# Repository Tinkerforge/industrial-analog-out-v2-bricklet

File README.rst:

Industrial Analog Out Bricklet 2.0
==================================

This repository contains the firmware source code and the hardware design
files. The documentation generator configs can be found at
https://github.com/Tinkerforge/generators

Repository Content
------------------

software/:
 * examples/: Examples for all supported languages
 * build/: Compiled files
 * src/: Source code of firmware
 * Makefile: Makefile to build project

hardware/:
 * Contains KiCad project files and additionally schematics as PDF

datasheets/:
 * Contains datasheets for sensors and complex ICs that are used

Hardware
--------

The hardware is designed with the open source EDA Suite KiCad
(http://www.kicad.org). Before you are able to open the files,
you have to install the Tinkerforge kicad-libraries
(https://github.com/Tinkerforge/kicad-libraries). You can either clone
them directly in hardware/ or clone them in a separate folder and
symlink them into hardware/
(ln -s kicad_path/kicad-libraries project_path/hardware). After that you
can open the .pro file in hardware/ with KiCad and from there view and
modify the schematics and the PCB layout.

Software
--------

If you want to do your own Brick/Bricklet firmware development we highly
recommend that you use our build environment setup script and read the
tutorial (https://www.tinkerforge.com/en/doc/Tutorials/Tutorial_Build_Environment/Tutorial.html).

To compile the C code we recommend you to install the newest GNU Arm Embedded
Toolchain (https://launchpad.net/gcc-arm-embedded/+download).
You also need to install bricklib2 (https://github.com/Tinkerforge/bricklib2).

You can either clone it directly in software/src/ or clone it in a
separate folder and symlink it into software/src/
(ln -s bricklib_path/bricklib2 project_path/software/src/). Finally make sure to
have CMake installed (http://www.cmake.org/cmake/resources/software.html).

After that you can build the firmware by invoking make in software/.
The firmware (.zbin) can then be found in software/build/ and uploaded
with brickv (click button "Flashing" on start screen).

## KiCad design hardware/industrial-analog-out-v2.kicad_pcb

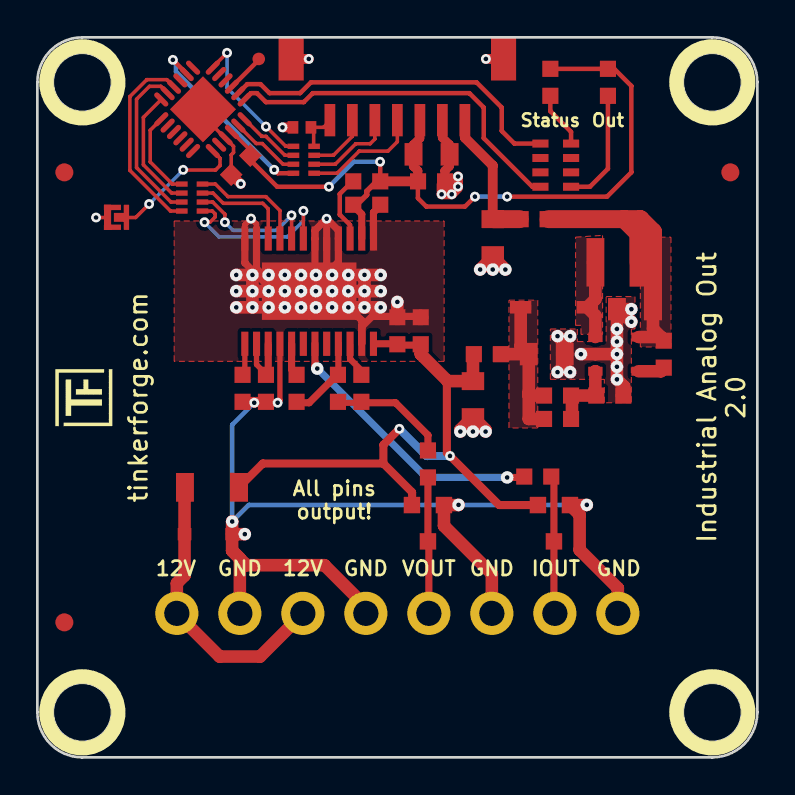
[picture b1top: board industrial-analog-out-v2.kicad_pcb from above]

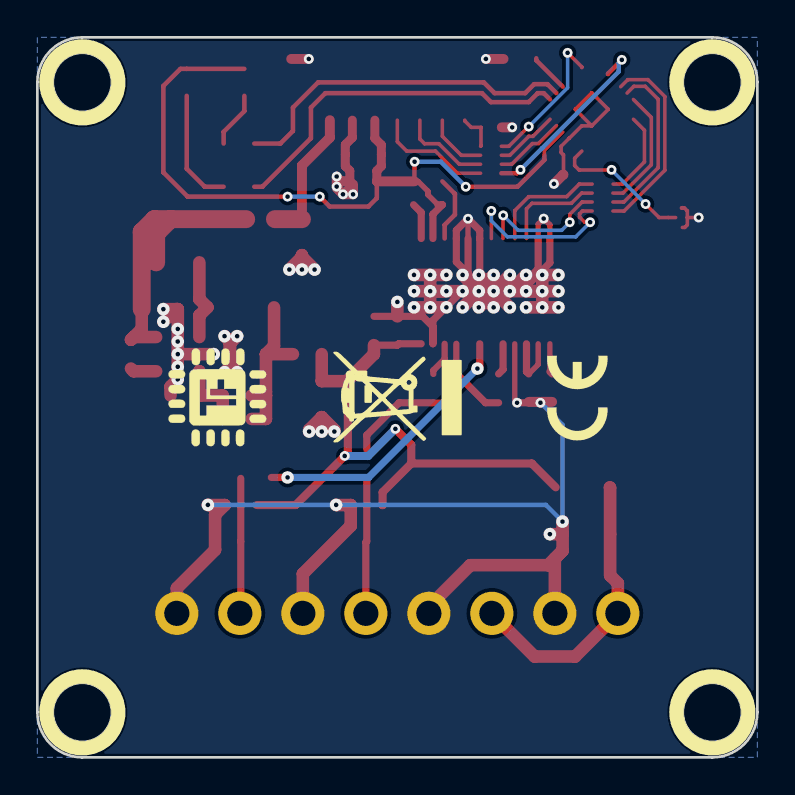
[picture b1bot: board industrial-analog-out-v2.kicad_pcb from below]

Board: 2 copper layers, 40.0 x 40.0 mm, 52 parts (2 on the bottom side), 42 nets.

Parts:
C1, C2, C5, C7: 4.7µF; C0805
C3: 10uF; C0805
C4: 270pF; C0603F
C6, C8, C9, C14: 100nF; C0603F
C10: 100pF; C0603F
C11: 1nF; C0603F
C12: 220pF; C0402F
C13: 1uF; C0603F
D1: B0520LW; SOD-123
D2, D3: DESD1P0RFW; SOT23-3
D4: CDSOD323-T15SC; SOD-323
D5, D6: blue; D0603F
F1: OZCJ0035FF2G; C1206
Fiducial_Mark: VAL**; Fiducial_Mark
Fiducial_Mark#2, Fiducial_Mark#3: VAL**; Fiducial_Mark
L1, L3, L4: FB; R0603F
L2: 10µH; NR3030
P1: CON-SENSOR2
P2: CONN_8; OQ_8P
P3: DEBUG; DEBUG_PAD
P4: BOOT; SolderJumper
R1: 1M; R0603F
R2: 13.3k; R0603F
R3: 118k; R0603F
R4: 10k; R0603F
R5: DNP; R0603F
R6, R7: 15; R0603F
R8: 10; R0603F
RP1, RP2: 82; 4X0402
RP3: 1k; 4X0603
U1: LMR62014X; SOT23-5
U2: XMC1100; QFN24-4x4mm-0.5mm
U3: DACX760; TSSOP24-44-PWR
U4, U5, U6, U7: DRILL; DRILL_NP
VAL: WEEE_7mm_back; WEEE_7mm
VAL#2: CE_5mm

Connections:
3V3: C3.1, C6.1, C13.1, C14.1, D5.1, D6.1, P1.3, R4.1, U2.10, U3.2
+5V: C1.2, L1.2, P1.1
+12V: C7.2, C9.2, C10.2, D2.2, D3.2, F1.1, L3.1, U3.24
GND: C1.1, C2.1, C3.2, C5.1, C6.2, C7.1, C8.2, C9.1, C10.1, C12.2, C13.2, C14.2, D2.1, D3.1, D4.2, P1.2, P1.EP, P2.2, P2.4, P2.6, P2.8, P4.1, R2.2, R5.2, U1.2, U2.9, U2.EXP, U3.1, U3.4, U3.5, U3.6, U3.11, U3.12, U3.16, U3.23
M-CLK: RP2.2, U3.8
M-CS: RP2.1, U3.7
M-MISO: RP2.3, U3.10
M-MOSI: RP2.4, U3.9
unnamed: C2.2, L1.1, L2.2, R1.1, U1.5
unnamed: C4.1, C5.2, D1.2, L3.2, R3.1
unnamed: C4.2, R2.1, R3.2, U1.3
unnamed: C8.1, U3.14, U3.15
unnamed: C11.1, R7.2, U3.21
unnamed: C11.2, U3.17
unnamed: C12.1, P1.7, RP1.4
unnamed: D1.1, L2.1, U1.1
unnamed: D2.3, L4.1, P2.5
unnamed: D3.3, P2.7, R8.1
unnamed: D4.1, F1.2, P2.1, P2.3
unnamed: D5.2, RP3.1
unnamed: D6.2, RP3.4
unnamed: L4.2, R6.1, R7.1
unnamed: P1.4, RP1.1
unnamed: P1.5, RP1.2
unnamed: P1.6, RP1.3
unnamed: P3.1, U2.15
unnamed: P4.2, U2.7
unnamed: R1.2, U1.4
unnamed: R4.2, U3.3
unnamed: R5.1, U3.13
unnamed: R6.2, U3.22
unnamed: R8.2, U3.19
unnamed: RP2.6, U2.24
unnamed: RP2.7, U2.23
unnamed: RP2.8, U2.22
unnamed: RP3.5, U2.13
unnamed: RP3.8, U2.14
P0.2: RP2.5, U2.1
S-CLK: RP1.7, U2.11
S-CS: RP1.8, U2.20
S-MISO: RP1.5, U2.18
S-MOSI: RP1.6, U2.12

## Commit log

2018-03-13 Add datasheet
2018-03-13 Add schematic
2018-03-13 Assign missing footprints
2018-03-13 Connect dac7760 to mcu
2018-03-13 Fix some pins
2018-03-13 Add layout
2018-03-13 Add all logos
2018-03-19 added second led, not fully routed
2018-03-19 routing finished, logo placement fixed
2018-03-19 fix status text
2018-04-10 Add auto-generated stub firmware
2018-04-10 Use correct pin defines for SPI, LEDs and debug
2018-04-11 Add DAC7760 driver
2018-04-12 Implement API
2018-04-12 Remove debug
2018-04-12 Use 100kHz baudrate (enough for 1000 changes/sec)
2018-04-17 Remove unused define
2018-04-17 Use USIC SPI instead of CHANNEL (removes warning)
2018-04-17 By default dac should be disabled
2018-04-17 Fix typo
2018-05-11 Rename files
2018-05-15 hardware: Remove special library
2018-06-06 fix fiducials
2018-06-18 Change capacitor footprint(s) to C0402F
2018-06-28 Fix readme
2018-07-11 Add Makefile with docker support
2018-07-11 Remove obsolete generate_makefile scripts
2018-07-11 Update directory structure and build instructions
2018-07-17 specify processor
2018-07-27 Channel status LED implementation
2018-07-31 Add 3d models (*.FCStd & *.step)
2018-07-31 Add PDF schematic
2018-08-17 remap for kicad 5.0, add sym table
2018-09-03 Add examples
2018-09-10 examples: Fix enable/disable calls
2018-09-21 Rename Channel LED to Out LED and remove unused channel parameter
2018-10-02 Add BOOTLOADER_FIX_POINTER_END define
2018-10-04 Add rev to changelog
2018-10-16 Remove in-development marker
2018-11-06 Add rust examples
2018-11-07 rust: Accept host names for ip connection, fix naming inconsistencies
2018-12-14 Add go examples.
2018-12-18 go: Change import path.
2018-12-18 go: Change import path again.
2018-12-20 rust: Reformat examples.
2019-01-24 mqtt: Add examples.
2019-01-24 mqtt: Fix example header.
2019-01-24 mqtt: Remove executable bit in example permissions.
2019-01-24 go: Minor example fixes.
2019-01-24 mqtt: Minor example fixes.
2019-05-29 Increase version for new release (changes in bricklib2)
2020-01-13 examples: Use python3 input instead of python2 raw_input.
2020-01-13 examples: mqtt: Remove trailing whitespace.
2020-03-16 Whitespace
2020-04-07 examples: rust: Always block when calling bindings functions.
2020-08-19 Add uc examples.
2020-08-25 uc: Fix whitespace
2020-08-27 uc: Fix warnings.
2020-09-02 uc: Add example driver note.
2021-02-09 fix inductor footprints
2021-10-25 Update KiCad link
    https://www.kicad.org/blog/2021/10/Avoid-links-to-former-kicad-domain/
2022-04-19 examples: uc: Rename TF_HalContext to TF_HAL.
2022-04-27 uc: Adapt to bindings changes
2022-07-06 Add license files.
2023-01-23 New standart layout. Switched to Kicad 6
2023-01-25 remove rescue lib stuff
2023-01-25 Data Cleanup
2025-10-04 Fix compatibility with new Docker build image (GCC 14.2.1)

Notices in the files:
hardware/industrial-analog-out-v2.kicad_pcb:
Copyright (©) 2023, T.Schneidermann
Copyright Tinkerforge GmbH 2023.
This documentation describes Open Hardware and is licensed under the
CERN OHL v. 1.1.
